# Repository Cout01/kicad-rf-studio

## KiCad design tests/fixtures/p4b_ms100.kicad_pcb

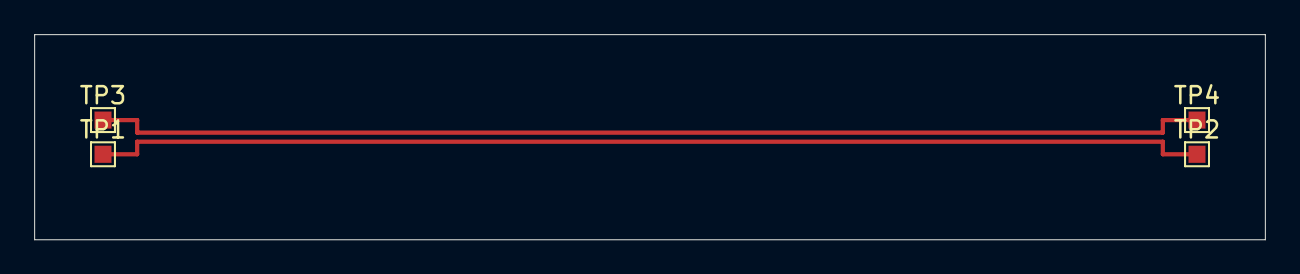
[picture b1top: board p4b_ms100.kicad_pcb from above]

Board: 4 copper layers, 72.0 x 12.0 mm, 4 parts (0 on the bottom side), 2 nets.

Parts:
TP1, TP2, TP3, TP4: TP; TestPoint_Pad_1.0x1.0mm

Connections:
D+: TP1.1, TP2.1
D-: TP3.1, TP4.1
